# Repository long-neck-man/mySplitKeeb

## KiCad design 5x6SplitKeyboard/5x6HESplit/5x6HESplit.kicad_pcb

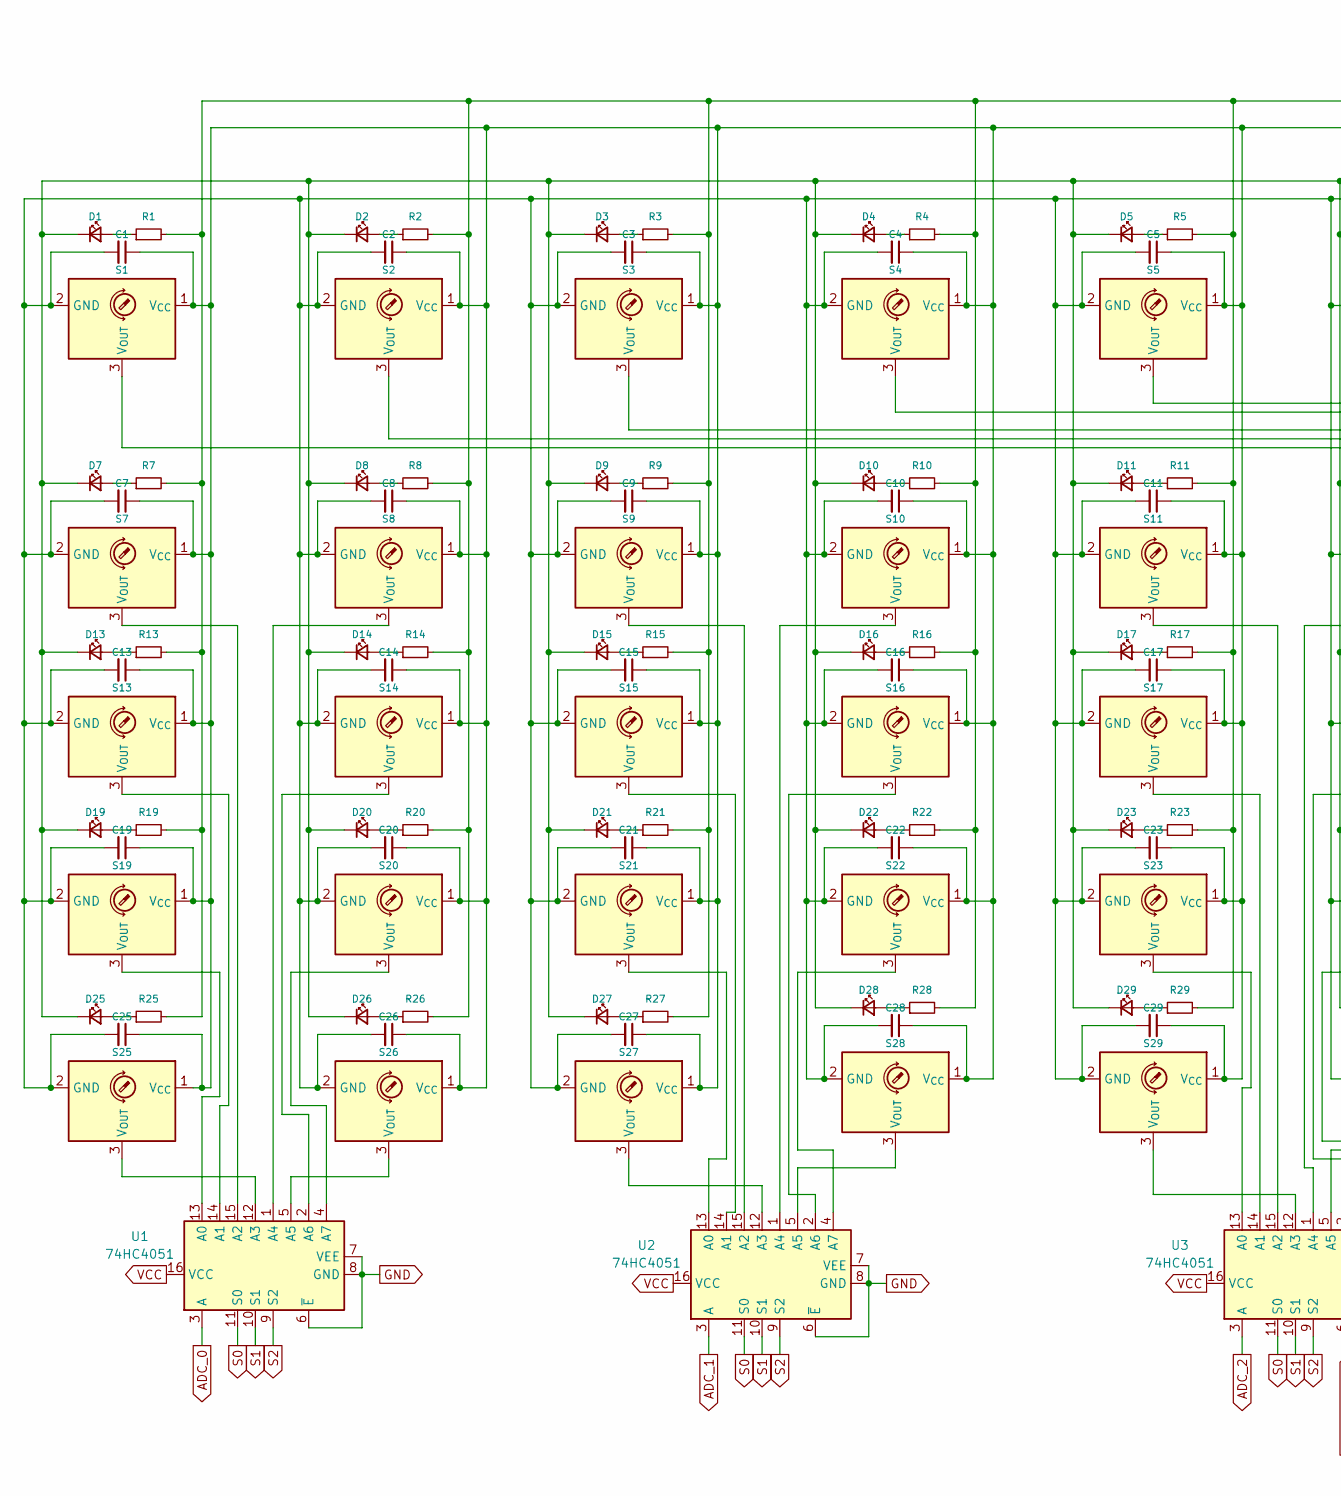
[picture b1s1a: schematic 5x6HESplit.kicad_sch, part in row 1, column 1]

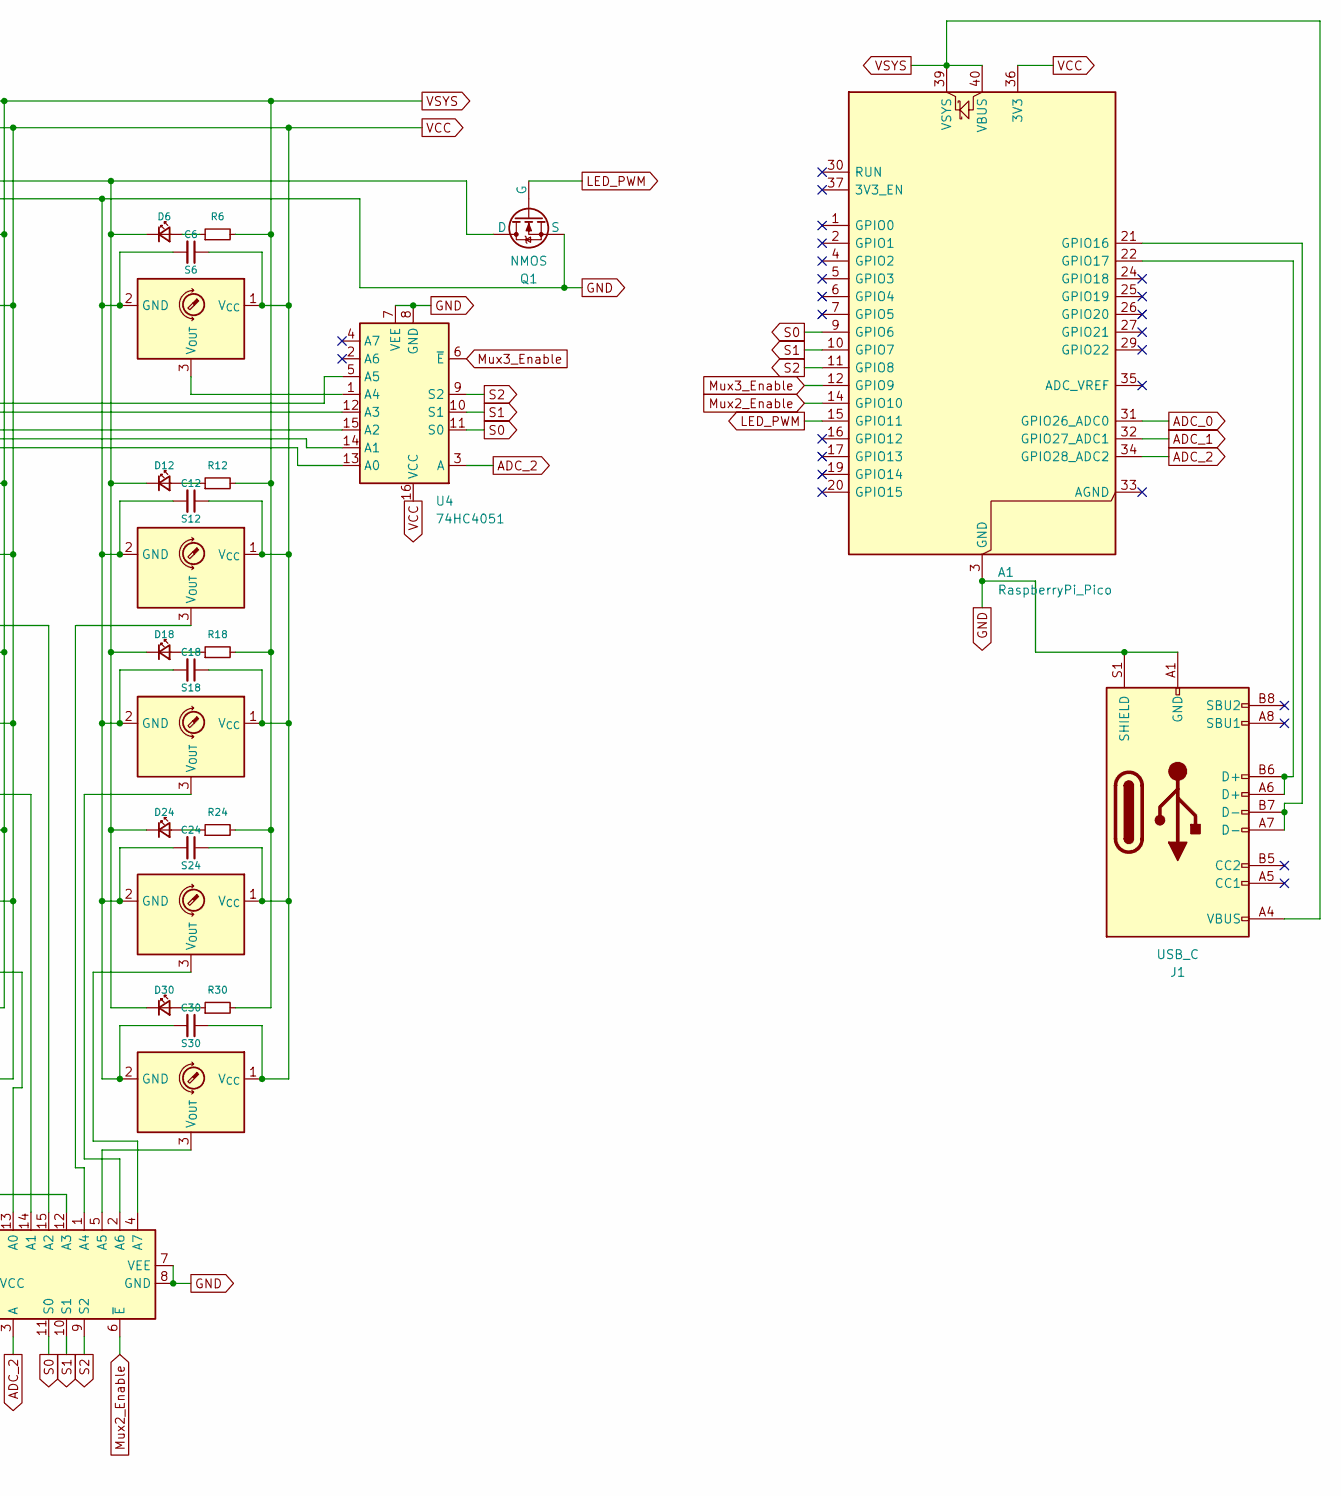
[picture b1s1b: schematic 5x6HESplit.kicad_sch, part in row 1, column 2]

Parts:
A1: RaspberryPi_Pico; RaspberryPi_Pico_Common_Unspecified
C1, C2, C3, C4, C5, C6, C7, C8, C9, C10, C11, C12, C13, C14, C15, C16, C17, C18, C19, C20, C21, C22, C23, C24, C25, C26, C27, C28, C29, C30: C_Small; C_0805_2012Metric_Pad1.18x1.45mm_HandSolder
D1, D2, D3, D4, D5, D6, D7, D8, D9, D10, D11, D12, D13, D14, D15, D16, D17, D18, D19, D20, D21, D22, D23, D24, D25, D26, D27, D28, D29, D30: LED_Small; LED_Everlight-SMD3528_3.5x2.8mm_67-21ST
J1: USB_C; USB_C_Receptacle_G-Switch_GT-USB-7010ASV
Q1: NMOS; SOT-23
R1, R2, R3, R4, R5, R6, R7, R8, R9, R10, R11, R12, R13, R14, R15, R16, R17, R18, R19, R20, R21, R22, R23, R24, R25, R26, R27, R28, R29, R30: R_Small; R_1206_3216Metric_Pad1.30x1.75mm_HandSolder
S1, S2, S3, S4, S5, S6, S7, S8, S9, S10, S11, S12, S13, S14, S15, S16, S17, S18, S19, S20, S21, S22, S23, S24, S25, S26, S27, S28, S29, S30: A1302xUA; TO-92S
U1, U2, U3, U4: 74HC4051; SOP-16_3.9x9.9mm_P1.27mm

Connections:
ADC_0: A1.31 (GPIO26_ADC0), U1.3 (A)
ADC_1: A1.32 (GPIO27_ADC1), U2.3 (A)
ADC_2: A1.34 (GPIO28_ADC2), U3.3 (A), U4.3 (A)
GND: A1.3 (GND), A1.8 (GND), A1.13 (GND), A1.18 (GND), A1.23 (GND), A1.28 (GND), A1.38 (GND), C1.2, C2.2, C3.2, C4.2, C5.2, C6.2, C7.2, C8.2, C9.2, C10.2, C11.2, C12.2, C13.2, C14.2, C15.2, C16.2, C17.2, C18.2, C19.2, C20.2, C21.2, C22.2, C23.2, C24.2, C25.2, C26.2, C27.2, C28.2, C29.2, C30.2, J1.A1 (GND), J1.A12 (GND), J1.B1 (GND), J1.B12 (GND), J1.S1 (SHIELD), Q1.3 (S), S1.2 (GND), S2.2 (GND), S3.2 (GND), S4.2 (GND), S5.2 (GND), S6.2 (GND), S7.2 (GND), S8.2 (GND), S9.2 (GND), S10.2 (GND), S11.2 (GND), S12.2 (GND), S13.2 (GND), S14.2 (GND), S15.2 (GND), S16.2 (GND), S17.2 (GND), S18.2 (GND), S19.2 (GND), S20.2 (GND), S21.2 (GND), S22.2 (GND), S23.2 (GND), S24.2 (GND), S25.2 (GND), S26.2 (GND), S27.2 (GND), S28.2 (GND), S29.2 (GND), S30.2 (GND), U1.6 (~E), U1.7 (VEE), U1.8 (GND), U2.6 (~E), U2.7 (VEE), U2.8 (GND), U3.7 (VEE), U3.8 (GND), U4.7 (VEE), U4.8 (GND)
LED_PWM: A1.15 (GPIO11), Q1.2 (G)
Mux2_Enable: A1.14 (GPIO10), U3.6 (~E)
Mux3_Enable: A1.12 (GPIO9), U4.6 (~E)
unnamed: A1.21 (GPIO16), J1.A7 (D-), J1.B7 (D-)
unnamed: A1.22 (GPIO17), J1.A6 (D+), J1.B6 (D+)
unnamed: D1.2 (A), R1.1
unnamed: D1.1 (K), D2.1 (K), D3.1 (K), D4.1 (K), D5.1 (K), D6.1 (K), D7.1 (K), D8.1 (K), D9.1 (K), D10.1 (K), D11.1 (K), D12.1 (K), D13.1 (K), D14.1 (K), D15.1 (K), D16.1 (K), D17.1 (K), D18.1 (K), D19.1 (K), D20.1 (K), D21.1 (K), D22.1 (K), D23.1 (K), D24.1 (K), D25.1 (K), D26.1 (K), D27.1 (K), D28.1 (K), D29.1 (K), D30.1 (K), Q1.1 (D)
unnamed: D2.2 (A), R2.1
unnamed: D3.2 (A), R3.1
unnamed: D4.2 (A), R4.1
unnamed: D5.2 (A), R5.1
unnamed: D6.2 (A), R6.1
unnamed: D7.2 (A), R7.1
unnamed: D8.2 (A), R8.1
unnamed: D9.2 (A), R9.1
unnamed: D10.2 (A), R10.1
unnamed: D11.2 (A), R11.1
unnamed: D12.2 (A), R12.1
unnamed: D13.2 (A), R13.1
unnamed: D14.2 (A), R14.1
unnamed: D15.2 (A), R15.1
unnamed: D16.2 (A), R16.1
unnamed: D17.2 (A), R17.1
unnamed: D18.2 (A), R18.1
unnamed: D19.2 (A), R19.1
unnamed: D20.2 (A), R20.1
unnamed: D21.2 (A), R21.1
unnamed: D22.2 (A), R22.1
unnamed: D23.2 (A), R23.1
unnamed: D24.2 (A), R24.1
unnamed: D25.2 (A), R25.1
unnamed: D26.2 (A), R26.1
unnamed: D27.2 (A), R27.1
unnamed: D28.2 (A), R28.1
unnamed: D29.2 (A), R29.1
unnamed: D30.2 (A), R30.1
unnamed: S1.3 (V_{OUT}), U4.13 (A0)
unnamed: S2.3 (V_{OUT}), U4.14 (A1)
unnamed: S3.3 (V_{OUT}), U4.15 (A2)
unnamed: S4.3 (V_{OUT}), U4.12 (A3)
unnamed: S5.3 (V_{OUT}), U4.5 (A5)
unnamed: S6.3 (V_{OUT}), U4.1 (A4)
unnamed: S7.3 (V_{OUT}), U1.15 (A2)
unnamed: S8.3 (V_{OUT}), U1.1 (A4)
unnamed: S9.3 (V_{OUT}), U2.15 (A2)
unnamed: S10.3 (V_{OUT}), U2.1 (A4)
unnamed: S11.3 (V_{OUT}), U3.15 (A2)
unnamed: S12.3 (V_{OUT}), U3.1 (A4)
unnamed: S13.3 (V_{OUT}), U1.14 (A1)
unnamed: S14.3 (V_{OUT}), U1.2 (A6)
unnamed: S15.3 (V_{OUT}), U2.14 (A1)
unnamed: S16.3 (V_{OUT}), U2.2 (A6)
unnamed: S17.3 (V_{OUT}), U3.14 (A1)
unnamed: S18.3 (V_{OUT}), U3.2 (A6)
unnamed: S19.3 (V_{OUT}), U1.13 (A0)
unnamed: S20.3 (V_{OUT}), U1.4 (A7)
unnamed: S21.3 (V_{OUT}), U2.13 (A0)
unnamed: S22.3 (V_{OUT}), U2.4 (A7)
unnamed: S23.3 (V_{OUT}), U3.13 (A0)
unnamed: S24.3 (V_{OUT}), U3.4 (A7)
unnamed: S25.3 (V_{OUT}), U1.12 (A3)
unnamed: S26.3 (V_{OUT}), U1.5 (A5)
unnamed: S27.3 (V_{OUT}), U2.12 (A3)
unnamed: S28.3 (V_{OUT}), U2.5 (A5)
unnamed: S29.3 (V_{OUT}), U3.12 (A3)
unnamed: S30.3 (V_{OUT}), U3.5 (A5)
S0: A1.9 (GPIO6), U1.11 (S0), U2.11 (S0), U3.11 (S0), U4.11 (S0)
S1: A1.10 (GPIO7), U1.10 (S1), U2.10 (S1), U3.10 (S1), U4.10 (S1)
S2: A1.11 (GPIO8), U1.9 (S2), U2.9 (S2), U3.9 (S2), U4.9 (S2)
VCC: A1.36 (3V3), C1.1, C2.1, C3.1, C4.1, C5.1, C6.1, C7.1, C8.1, C9.1, C10.1, C11.1, C12.1, C13.1, C14.1, C15.1, C16.1, C17.1, C18.1, C19.1, C20.1, C21.1, C22.1, C23.1, C24.1, C25.1, C26.1, C27.1, C28.1, C29.1, C30.1, S1.1 (V_{CC}), S2.1 (V_{CC}), S3.1 (V_{CC}), S4.1 (V_{CC}), S5.1 (V_{CC}), S6.1 (V_{CC}), S7.1 (V_{CC}), S8.1 (V_{CC}), S9.1 (V_{CC}), S10.1 (V_{CC}), S11.1 (V_{CC}), S12.1 (V_{CC}), S13.1 (V_{CC}), S14.1 (V_{CC}), S15.1 (V_{CC}), S16.1 (V_{CC}), S17.1 (V_{CC}), S18.1 (V_{CC}), S19.1 (V_{CC}), S20.1 (V_{CC}), S21.1 (V_{CC}), S22.1 (V_{CC}), S23.1 (V_{CC}), S24.1 (V_{CC}), S25.1 (V_{CC}), S26.1 (V_{CC}), S27.1 (V_{CC}), S28.1 (V_{CC}), S29.1 (V_{CC}), S30.1 (V_{CC}), U1.16 (VCC), U2.16 (VCC), U3.16 (VCC), U4.16 (VCC)
VSYS: A1.39 (VSYS), A1.40 (VBUS), J1.A4 (VBUS), J1.A9 (VBUS), J1.B4 (VBUS), J1.B9 (VBUS), R1.2, R2.2, R3.2, R4.2, R5.2, R6.2, R7.2, R8.2, R9.2, R10.2, R11.2, R12.2, R13.2, R14.2, R15.2, R16.2, R17.2, R18.2, R19.2, R20.2, R21.2, R22.2, R23.2, R24.2, R25.2, R26.2, R27.2, R28.2, R29.2, R30.2

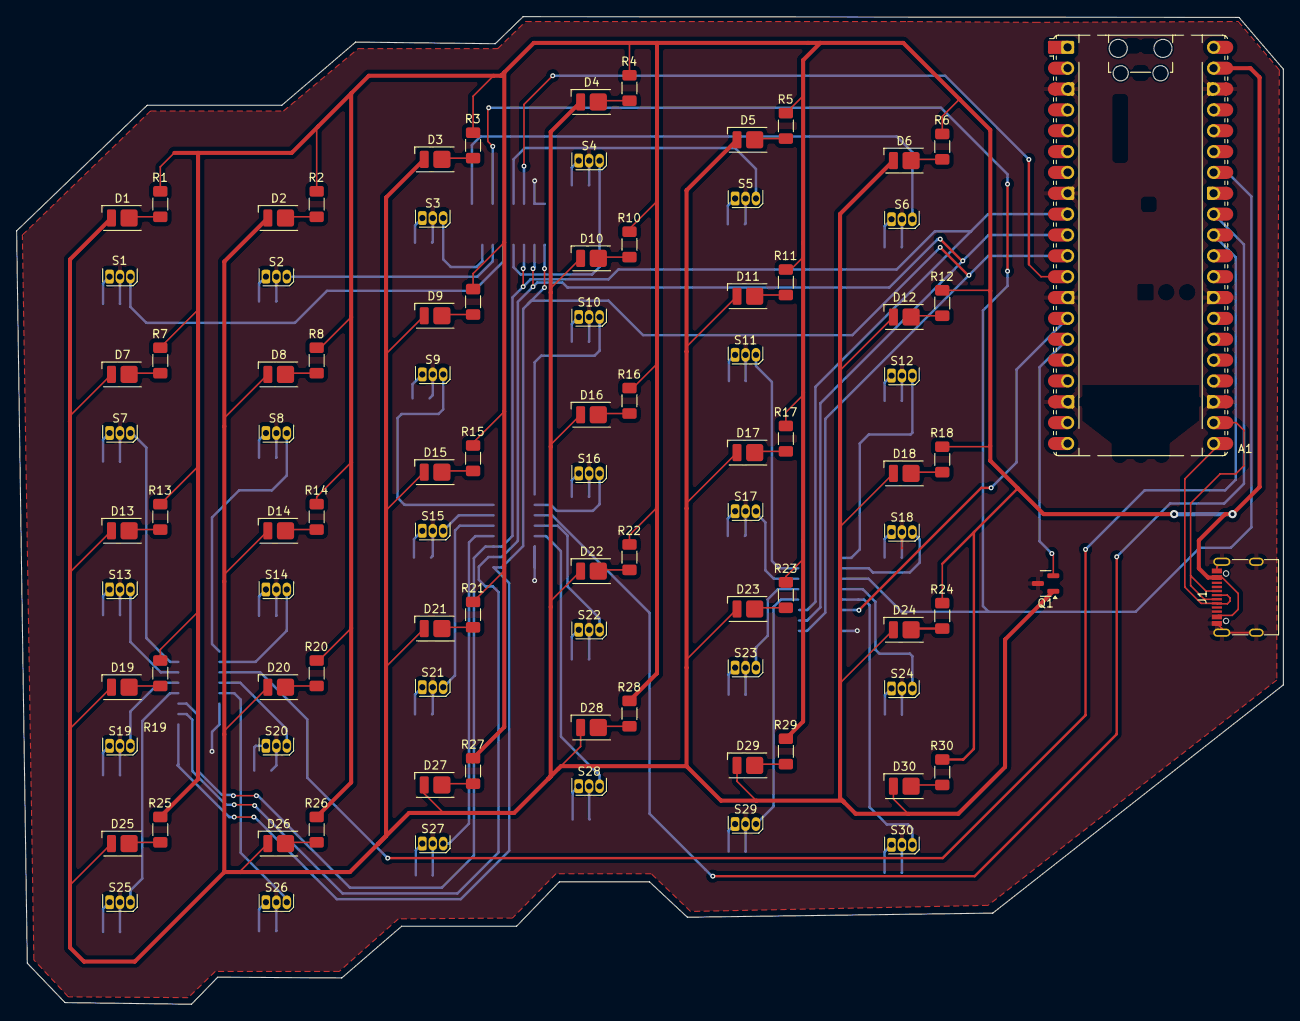
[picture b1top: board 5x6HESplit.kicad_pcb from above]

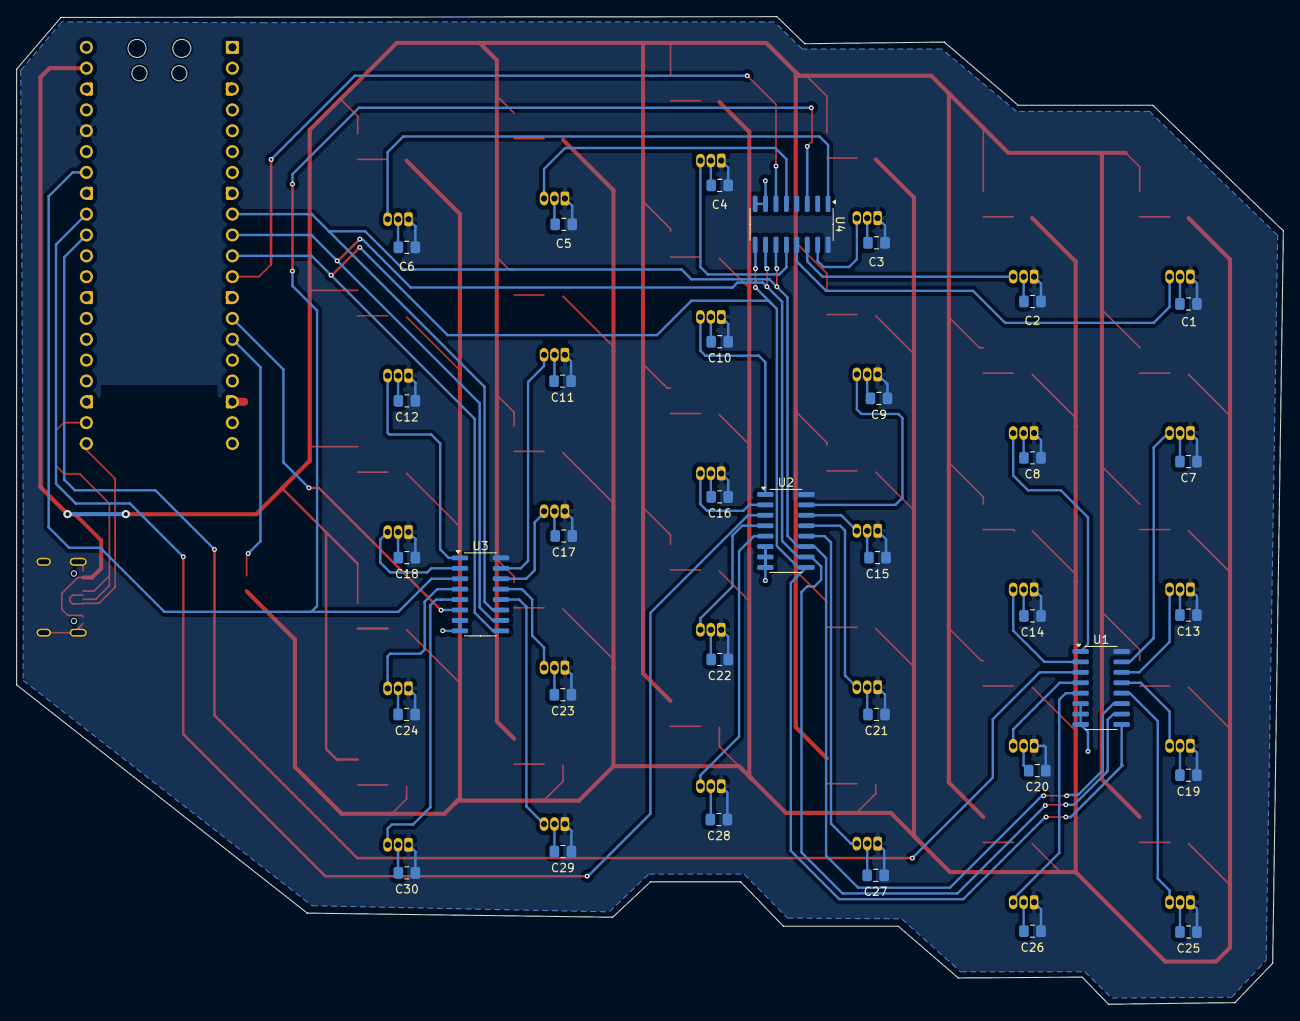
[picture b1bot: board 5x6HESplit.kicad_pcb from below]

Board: 2 copper layers, 154.3 x 120.3 mm, 127 parts (34 on the bottom side), 75 nets.

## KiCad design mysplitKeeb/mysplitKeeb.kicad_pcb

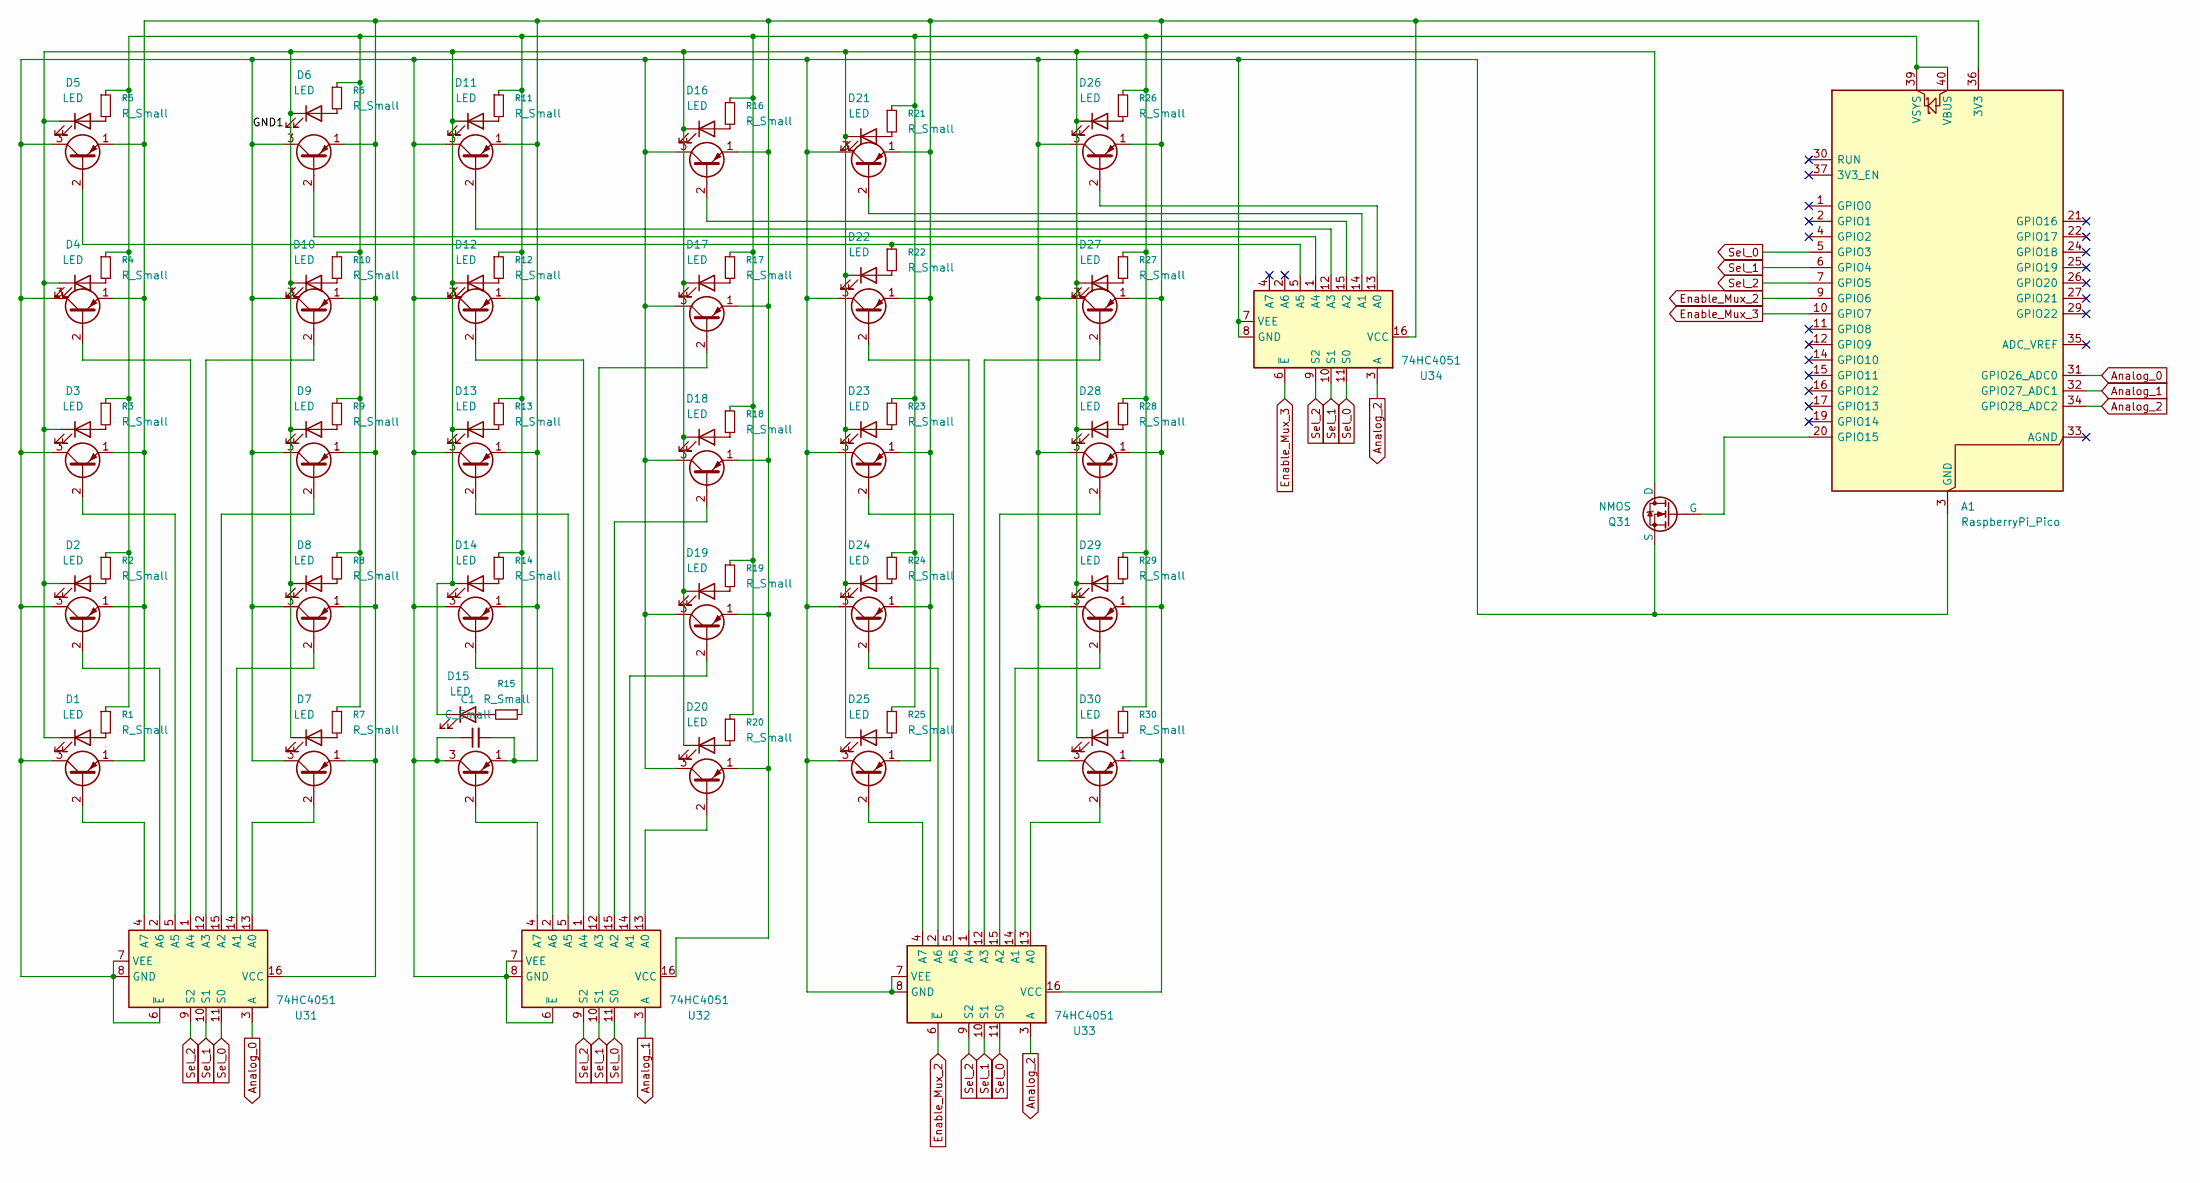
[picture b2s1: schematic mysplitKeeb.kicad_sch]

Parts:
A1: RaspberryPi_Pico; RaspberryPi_Pico_Common_Unspecified
C1: C_Small
D1, D2, D3, D4, D5, D6, D7, D8, D9, D10, D11, D12, D13, D14, D15, D16, D17, D18, D19, D20, D21, D22, D23, D24, D25, D26, D27, D28, D29, D30: LED; LED_Everlight-SMD3528_3.5x2.8mm_67-21ST
Q1, Q2, Q3, Q4, Q5, Q6, Q7, Q8, Q9, Q10, Q11, Q12, Q13, Q14, Q15, Q16, Q17, Q18, Q19, Q20, Q21, Q22, Q23, Q24, Q25, Q26, Q27, Q28, Q29, Q30: Q_PNP_EBC; TO-92_Inline
Q31: NMOS; SOT-23
R1, R2, R3, R4, R5, R6, R7, R8, R9, R10, R11, R12, R13, R14, R15, R16, R17, R18, R19, R20, R21, R22, R23, R24, R25, R26, R27, R28, R29, R30: R_Small; R_1206_3216Metric_Pad1.30x1.75mm_HandSolder
U31, U32, U33, U34: 74HC4051; SOIC-16_3.9x9.9mm_P1.27mm

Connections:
/GND1: A1.3 (GND), A1.8 (GND), A1.13 (GND), A1.18 (GND), A1.23 (GND), A1.28 (GND), A1.38 (GND), C1.1, Q1.3 (C), Q2.3 (C), Q3.3 (C), Q4.3 (C), Q5.3 (C), Q6.3 (C), Q7.3 (C), Q8.3 (C), Q9.3 (C), Q10.3 (C), Q11.3 (C), Q12.3 (C), Q13.3 (C), Q14.3 (C), Q15.3 (C), Q16.3 (C), Q17.3 (C), Q18.3 (C), Q19.3 (C), Q20.3 (C), Q21.3 (C), Q22.3 (C), Q23.3 (C), Q24.3 (C), Q25.3 (C), Q26.3 (C), Q27.3 (C), Q28.3 (C), Q29.3 (C), Q30.3 (C), Q31.3 (S), U31.6 (~E), U31.7 (VEE), U31.8 (GND), U32.6 (~E), U32.7 (VEE), U32.8 (GND), U33.7 (VEE), U33.8 (GND), U34.7 (VEE), U34.8 (GND)
Analog_0: A1.31 (GPIO26_ADC0), U31.3 (A)
Analog_1: A1.32 (GPIO27_ADC1), U32.3 (A)
Analog_2: A1.34 (GPIO28_ADC2), U33.3 (A), U34.3 (A)
Enable_Mux_2: A1.9 (GPIO6), U33.6 (~E)
Enable_Mux_3: A1.10 (GPIO7), U34.6 (~E)
unnamed: A1.36 (3V3), C1.2, Q1.1 (E), Q2.1 (E), Q3.1 (E), Q4.1 (E), Q5.1 (E), Q6.1 (E), Q7.1 (E), Q8.1 (E), Q9.1 (E), Q10.1 (E), Q11.1 (E), Q12.1 (E), Q13.1 (E), Q14.1 (E), Q15.1 (E), Q16.1 (E), Q17.1 (E), Q18.1 (E), Q19.1 (E), Q20.1 (E), Q21.1 (E), Q22.1 (E), Q23.1 (E), Q24.1 (E), Q25.1 (E), Q26.1 (E), Q27.1 (E), Q28.1 (E), Q29.1 (E), Q30.1 (E), U31.16 (VCC), U32.16 (VCC), U33.16 (VCC), U34.16 (VCC)
unnamed: A1.20 (GPIO15), Q31.2 (G)
unnamed: A1.39 (VSYS), A1.40 (VBUS), R1.1, R2.1, R3.1, R4.1, R5.1, R6.1, R7.1, R8.1, R9.1, R10.1, R11.1, R12.1, R13.1, R14.1, R15.1, R16.1, R17.1, R18.1, R19.1, R20.1, R21.1, R23.1, R24.1, R25.1, R26.1, R27.1, R28.1, R29.1, R30.1
unnamed: D1.2 (A), R1.2
unnamed: D1.1 (K), D2.1 (K), D3.1 (K), D4.1 (K), D5.1 (K), D6.1 (K), D7.1 (K), D8.1 (K), D9.1 (K), D10.1 (K), D11.1 (K), D12.1 (K), D13.1 (K), D14.1 (K), D15.1 (K), D16.1 (K), D17.1 (K), D18.1 (K), D19.1 (K), D20.1 (K), D21.1 (K), D22.1 (K), D23.1 (K), D24.1 (K), D25.1 (K), D26.1 (K), D27.1 (K), D28.1 (K), D29.1 (K), D30.1 (K), Q31.1 (D)
unnamed: D2.2 (A), R2.2
unnamed: D3.2 (A), R3.2
unnamed: D4.2 (A), R4.2
unnamed: D5.2 (A), R5.2
unnamed: D6.2 (A), R6.2
unnamed: D7.2 (A), R7.2
unnamed: D8.2 (A), R8.2
unnamed: D9.2 (A), R9.2
unnamed: D10.2 (A), R10.2
unnamed: D11.2 (A), R11.2
unnamed: D12.2 (A), R12.2
unnamed: D13.2 (A), R13.2
unnamed: D14.2 (A), R14.2
unnamed: D15.2 (A), R15.2
unnamed: D16.2 (A), R16.2
unnamed: D17.2 (A), R17.2
unnamed: D18.2 (A), R18.2
unnamed: D19.2 (A), R19.2
unnamed: D20.2 (A), R20.2
unnamed: D21.2 (A), R21.2
unnamed: D22.2 (A), R22.2
unnamed: D23.2 (A), R23.2
unnamed: D24.2 (A), R24.2
unnamed: D25.2 (A), R25.2
unnamed: D26.2 (A), R26.2
unnamed: D27.2 (A), R27.2
unnamed: D28.2 (A), R28.2
unnamed: D29.2 (A), R29.2
unnamed: D30.2 (A), R30.2
unnamed: Q1.2 (B), R22.1, U34.5 (A5)
unnamed: Q2.2 (B), U34.1 (A4)
unnamed: Q3.2 (B), U34.12 (A3)
unnamed: Q4.2 (B), U34.15 (A2)
unnamed: Q5.2 (B), U34.14 (A1)
unnamed: Q6.2 (B), U34.13 (A0)
unnamed: Q7.2 (B), U31.1 (A4)
unnamed: Q8.2 (B), U31.12 (A3)
unnamed: Q9.2 (B), U32.1 (A4)
unnamed: Q10.2 (B), U32.12 (A3)
unnamed: Q11.2 (B), U33.1 (A4)
unnamed: Q12.2 (B), U33.12 (A3)
unnamed: Q13.2 (B), U31.5 (A5)
unnamed: Q14.2 (B), U31.2 (A6)
unnamed: Q15.2 (B), U31.15 (A2)
unnamed: Q16.2 (B), U31.14 (A1)
unnamed: Q17.2 (B), U32.5 (A5)
unnamed: Q18.2 (B), U32.2 (A6)
unnamed: Q19.2 (B), U32.15 (A2)
unnamed: Q20.2 (B), U32.14 (A1)
unnamed: Q21.2 (B), U33.5 (A5)
unnamed: Q22.2 (B), U33.2 (A6)
unnamed: Q23.2 (B), U33.15 (A2)
unnamed: Q24.2 (B), U33.14 (A1)
unnamed: Q25.2 (B), U31.4 (A7)
unnamed: Q26.2 (B), U31.13 (A0)
unnamed: Q27.2 (B), U32.4 (A7)
unnamed: Q28.2 (B), U32.13 (A0)
unnamed: Q29.2 (B), U33.4 (A7)
unnamed: Q30.2 (B), U33.13 (A0)
Sel_0: A1.5 (GPIO3), U31.11 (S0), U32.11 (S0), U33.11 (S0), U34.11 (S0)
Sel_1: A1.6 (GPIO4), U31.10 (S1), U32.10 (S1), U33.10 (S1), U34.10 (S1)
Sel_2: A1.7 (GPIO5), U31.9 (S2), U32.9 (S2), U33.9 (S2), U34.9 (S2)

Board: 2 copper layers, 96 parts (4 on the bottom side), 73 nets, no tracks yet.

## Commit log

2025-05-01 basic LHS PCB
2025-05-07 started new project
2025-05-07 Minor changes to trace width and added a schematic pdf
